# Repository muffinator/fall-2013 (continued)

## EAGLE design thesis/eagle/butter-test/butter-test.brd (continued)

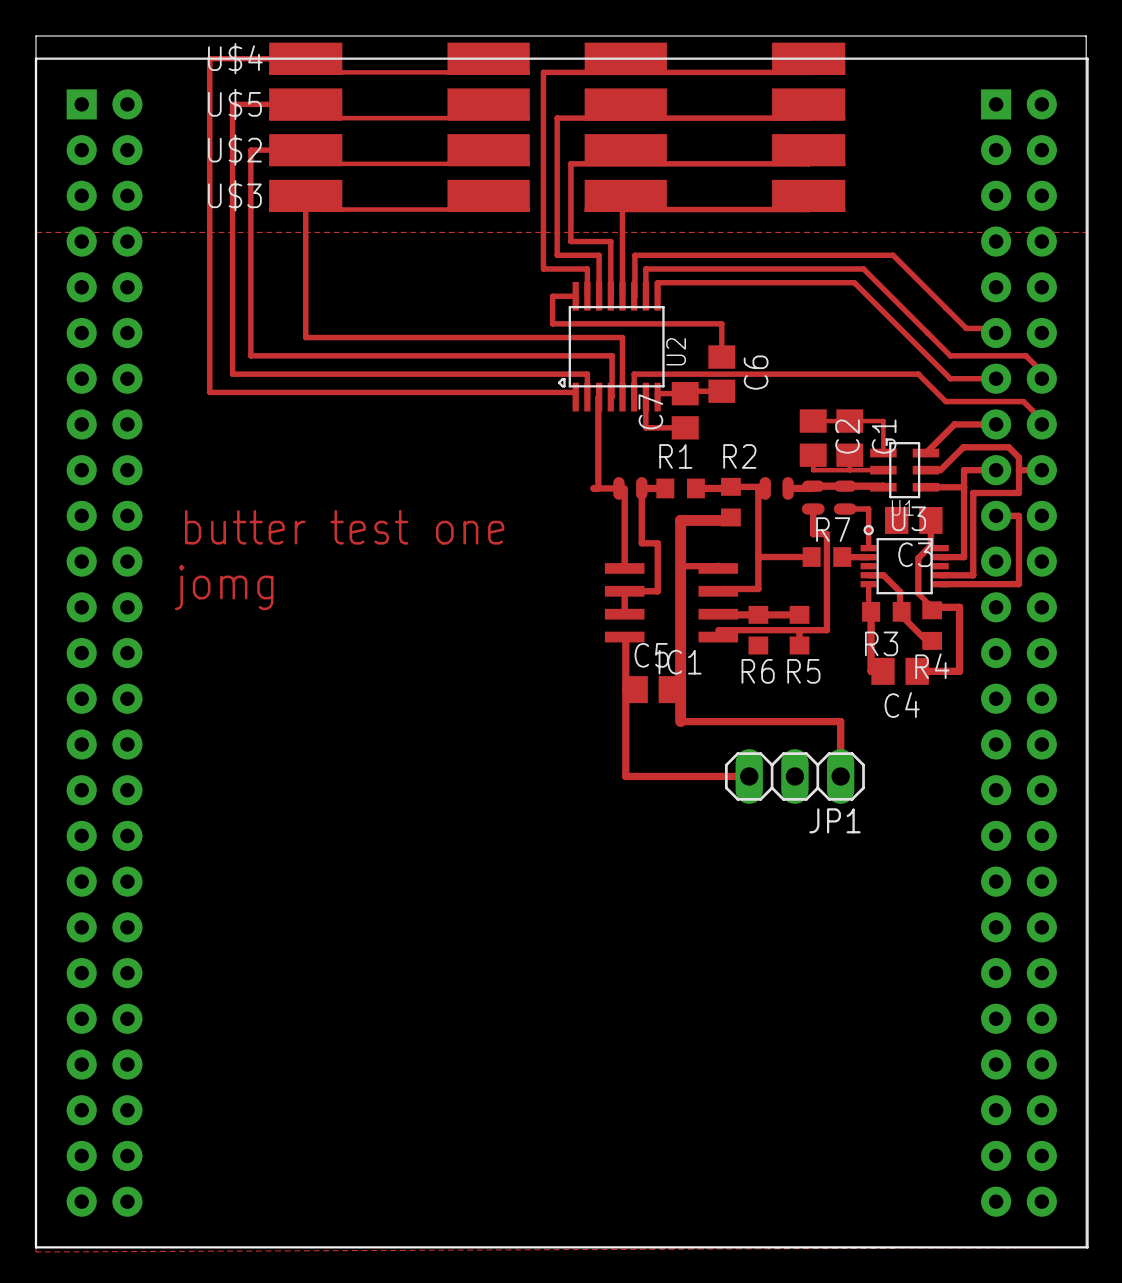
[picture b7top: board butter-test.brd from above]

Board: 2 copper layers, 58.3 x 67.3 mm, 28 parts (0 on the bottom side), 29 nets.

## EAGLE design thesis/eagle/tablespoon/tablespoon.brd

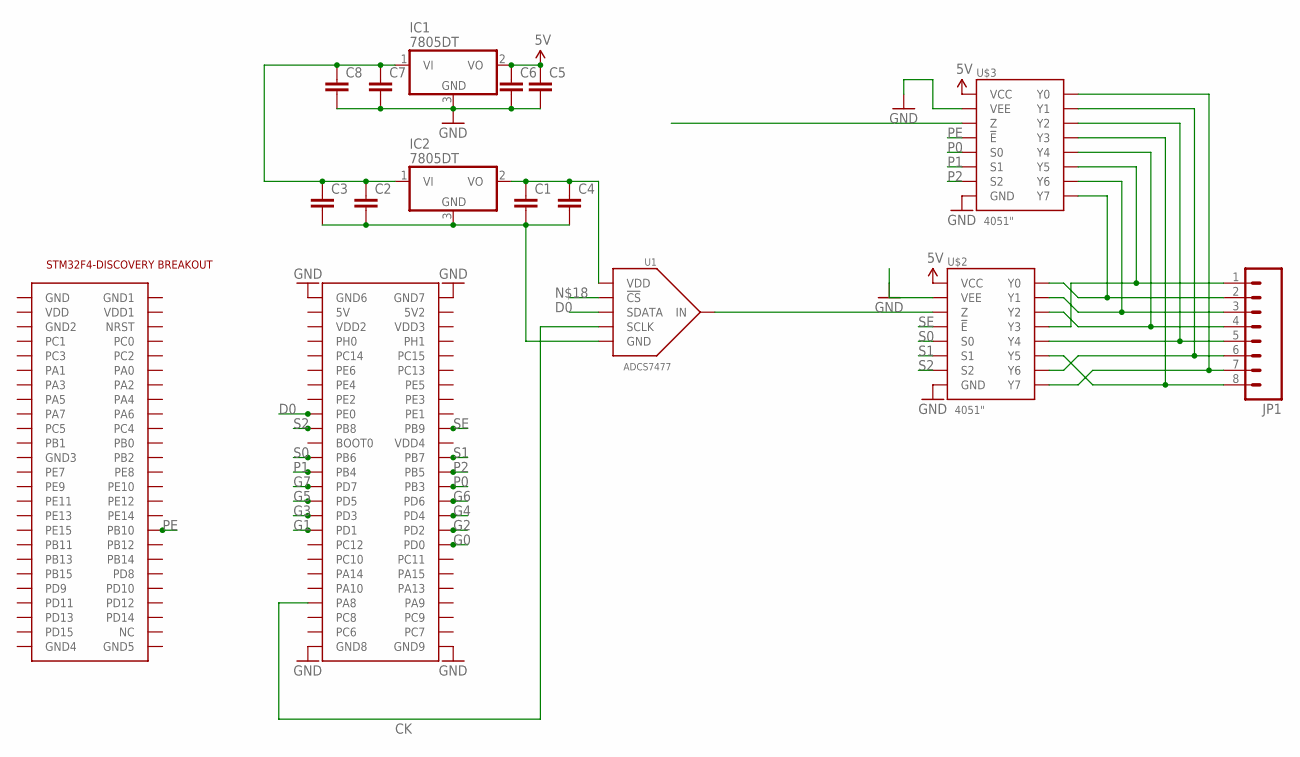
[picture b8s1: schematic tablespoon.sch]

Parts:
C1, C2, C3, C4, C5, C6, C7, C8: C-EUC0805; C0805
IC1, IC2: 7805DT; TO252
JP1: M08LONGPADS; 1X08_LONGPADS
U1: ADCS7477; SOT-23-6
U$1: STM32F4-DISCOVERY
U$2, U$3: 4051"; TSSOP-16

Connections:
5V: C5.1, C6.1, IC1.2 (VO), U$2.P$16 (VCC), U$3.P$16 (VCC)
CK: U1.P$4 (SCLK), U$1.P$93 (PA8)
D0: U1.P$5 (SDATA), U$1.P$67 (PE0)
G0: U$1.P$86 (PD0)
G1: U$1.P$83 (PD1)
G2: U$1.P$84 (PD2)
G3: U$1.P$81 (PD3)
G4: U$1.P$82 (PD4)
G5: U$1.P$79 (PD5)
G6: U$1.P$80 (PD6)
G7: U$1.P$77 (PD7)
GND: C5.2, C6.2, C7.2, C8.2, IC1.3 (GND), U$1.P$51 (GND6), U$1.P$52 (GND7), U$1.P$99 (GND8), U$1.P$100 (GND9), U$2.P$7 (VEE), U$2.P$8 (GND), U$3.P$7 (VEE), U$3.P$8 (GND)
unnamed: U1.P$3 (IN), U$2.P$3 (Z)
unnamed: C1.1, C4.1, IC2.2 (VO), U1.P$1 (VDD)
unnamed: C1.2, C2.2, C3.2, C4.2, IC2.3 (GND), U1.P$2 (GND)
unnamed: C2.1, C3.1, C7.1, C8.1, IC1.1 (VI), IC2.1 (VI)
unnamed: JP1.4, U$2.P$15 (Y2), U$3.P$1 (Y4)
unnamed: JP1.7, U$2.P$4 (Y7), U$3.P$13 (Y0)
unnamed: JP1.5, U$2.P$1 (Y4), U$3.P$15 (Y2)
unnamed: JP1.8, U$2.P$5 (Y5), U$3.P$12 (Y3)
unnamed: JP1.1, U$2.P$12 (Y3), U$3.P$5 (Y5)
unnamed: JP1.2, U$2.P$13 (Y0), U$3.P$4 (Y7)
unnamed: JP1.3, U$2.P$14 (Y1), U$3.P$2 (Y6)
unnamed: JP1.6, U$2.P$2 (Y6), U$3.P$14 (Y1)
P0: U$1.P$78 (PB3), U$3.P$11 (S0)
P1: U$1.P$75 (PB4), U$3.P$10 (S1)
P2: U$1.P$76 (PB5), U$3.P$9 (S2)
PE: U$1.P$34 (PB10), U$3.P$6 (!E)
S0: U$1.P$73 (PB6), U$2.P$11 (S0)
S1: U$1.P$74 (PB7), U$2.P$10 (S1)
S2: U$1.P$69 (PB8), U$2.P$9 (S2)
SE: U$1.P$70 (PB9), U$2.P$6 (!E)

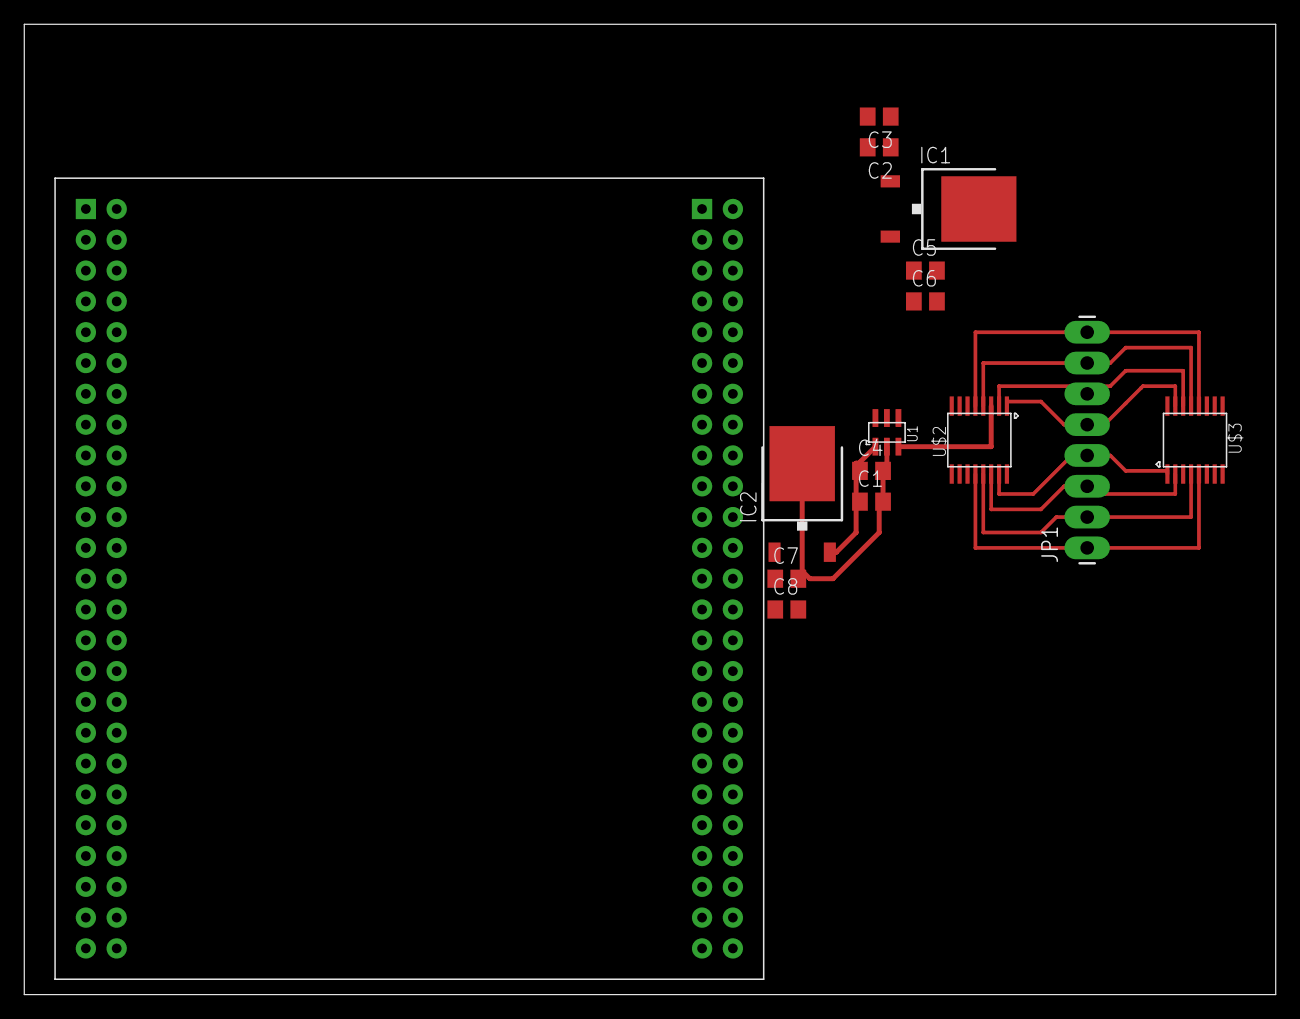
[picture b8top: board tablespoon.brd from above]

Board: 2 copper layers, 103.2 x 80.0 mm, 15 parts (0 on the bottom side), 24 nets.

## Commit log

2013-09-10 added readme
2013-09-10 added ps1 and ps2
2013-09-10 updated ps2
2013-09-10 added ps2, edited!
2013-09-11 finished writing up problems, just need to put in schematics
2013-09-11 added transistor datasheets
2013-09-11 corrected Vbe on problem 2
2013-09-11 finished ps2
2013-09-18 added ps3
2013-09-18 added gitignore
2013-09-18 finished problems 4 and 5
2013-09-19 finished text for pset 3
2013-09-19 finished pictures for pset 3
2013-09-19 added ce-max image
2013-09-19 almost finished ps3
2013-09-19 fixed pictures
2013-09-19 compiled final pset
2013-09-19 added extra credit section
2013-10-01 added ps4
2013-10-01 added pdf and tex
2013-10-01 finished pset 4
2013-10-01 added remaining ps4 images
2013-10-07 added bypassing caps on cascode current sources.
2013-10-07 pdflatex'd with new images
2013-10-16 added 6.332
2013-10-16 added solns for ps1
2013-10-17 added 6.301 ps5
2013-10-17 added ps5 images
2013-10-17 fixed cap label
2013-10-17 fixed node
2013-10-25 added 6.332 pset stuff
2013-10-25 added ps4 and 5 to 6.301
2013-10-25 added 6.332 project folder and ps2 info
2013-10-25 cleaning up
2013-11-05 added ps6 and 7
2013-11-12 added ps5 and 6 solns
2013-11-17 added ps4 solns and npn spice model example
2013-11-17 worked on resonant rectifier a bit
2013-11-17 added resonant-rect-orig
2013-11-17 worked on resonant rect: now 2.45 GHz
2013-11-18 took data modifying l_r and Vo and Iin
2013-11-18 added roberge's lab 2
2013-11-18 added no .raws to gitignore
2013-11-18 added 6.332 ps4
2013-11-18 cleanup + adding solutions
2013-11-18 nailed down Lr, Vo, and Iin
2013-11-18 data
2013-11-18 deleted .raws
2013-11-18 added rectifier layout
2013-11-18 added .fft to gitignore
2013-11-19 added ps8
2013-11-22 finished pset 8
2013-11-22 added recitation notes
2013-12-11 ps8 cleanup
2013-12-11 working on ps8 solns
2013-12-11 finished ps8 solns
2013-12-16 almost done with 332 project
2013-12-16 added ps9
2013-12-16 added final stuff for 6.301
2013-12-22 added psc
2013-12-22 added thesis
2014-10-31 iterates through all nodes specified for .op and prints out dictionaries for each simulation
2014-10-31 added sent proposal
2014-12-17 sim.py structure written
2014-12-17 removed output.txt
2014-12-17 added n-resistor attempt
2014-12-17 added d3 viewers and json examples
2014-12-17 added two-resistor network solver
2014-12-25 added some eagle files and .gitinit file
2014-12-25 added bom
2014-12-25 cleaning up ugly eagle files
2014-12-25 added eagle files for reals now
2014-12-25 added new flexible methods to sim.py, deleted sim.net, got n.py pretty much all the way working
2014-12-25 started playing with AC analysis
2014-12-25 stopped tracking json files
2014-12-25 ignoring datasheets, json files, and ugly eagle files
2014-12-26 ignoring .pyc's
2014-12-26 added stm32f4 part library
2014-12-26 added stm32f4 breakout to design, starting with two ADCs and two multiplexers
2014-12-27 started simulating breadboard rail drive solutions
2014-12-28 testing voltage and current based probing
2014-12-28 added analog switch to bom - will probably turn into nfet and pfet
2014-12-28 added rails to library
2014-12-28 started designing rail interface
2015-01-18 added breakout board
2015-01-18 added adc-in sim
2015-01-18 added breadboard 3d models
2015-01-18 voltage default played with
2015-01-18 added gluespot
2015-02-12 updated gitignore
2015-02-17 whatever, fuck it
2015-03-09 added muxes and pga to bom
2015-03-09 rev 1a!
2015-03-09 was playing with ADC input circuitry. I added the passive divider + offset circuit (R1 and R2) and decided to play with the other gain options
2015-03-09 first etch board rev. Doesn't have the switches on it (those have high capacitance, too :()
2015-03-10 added butter stm32 project
2015-03-14 butter folder commit
2015-03-14 renamed butter to butter-f3
2015-03-27 have timer two working and still trying to get the DMA working. realized a couple things - i'm using the CC interrupt on the timer, not the update one, and the DMA was configured for using the update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
2015-03-27 moved thesis parts to /thesis
2015-03-27 moved proposal stuff
2015-03-27 shrug
2015-03-30 output DMA to GPIOB working
2015-03-30 got 16MHz data->GPIOB working
2015-03-31 have triggered sampling working
2015-04-01 non-circular one-shot working, with end-of-transfer reset
2015-04-03 non-circular one-shot with timer 2 update interrupt disabling timer 1, then timer 1 re-enabled by other fuction
2015-04-06 have one-shot triggered by timer reset working
2015-04-06 send raw ADC buffer over USB
2015-04-07 maybe decoding works?
2015-04-08 have data-rearrangement working
2015-04-09 committing
2015-04-10 sending one datapoint to node.js working
2015-05-28 started rlc.py, fixed random metlist generation
2015-05-28 latest butter work
2015-05-28 got resistor force diagram working
2015-05-28 latest thesis writing
2015-06-02 got rlc to do steady state resistors with simple method
2015-06-02 modified note
2015-06-04 got AC simulation parsing working in sim.py, working on generating the impedance matrix for any given AC frequency data
2015-06-04 not sure what's new here, but updated butter board
2015-06-04 update gitignore
2015-06-25 streamlined voltage sampling
2015-06-25 worked on thesis a bit, started writing about resistor simulation
2015-06-25 added mosfet to library
2015-06-25 started working on a tablespoon of butter
2015-06-25 so I can read inductors and capacitors and resistors, but i haven't figured out how to select the correct frequency reading for each component yet. working on that now!
2015-06-25 r,l,and cboop are now only two dimensions
2015-06-25 have resistors working, need to get the diagonal of L and C
2015-06-25 made the frames smaller
2015-06-26 re-added zboop to do the diagonal
2015-06-26 can't seem to get the diagonal impedance method working...
2015-06-30 wrote so much more on my theeesiiiis
2015-06-30 rlc images for thesis
2015-07-09 added teaspoon!
2015-07-09 worked on thesis more?
2015-07-09 teaspoon as we know it (multiply by 2 issue)
2015-07-10 grounding, muxing, and ADCing all working. x2 fixed (had to do with number of packets sent over USB?????
2015-07-10 just a spoonful of sugar makes the medicine go down - python cereal controler for tsp
2015-07-10 took away those nasty usb subroutines and defines
2015-07-10 nona dose pesky blegh files, all right?!
2015-07-10 oh when you're done with that teaspoon, do i gotta tablespoon fer you!
2015-07-10 showing gjs this - pass 1
2015-07-11 if you slow down sampling, things get more accurate. re-wrote sample trigger 's' so it has a timing parameter and mux trigger 'm' so it has a gate parameter.
2015-07-19 peak detecting and thiiings
2015-07-19 moved all the eagle files into folders
2015-07-19 moved all the eagle stuff from /eagle to individual folders
2015-07-19 adding sine wavetable
2015-07-19 added .cir to gitignore
2015-07-19 switch-break
2015-07-19 made inductor and capacitor SVGs, played around with trying to graph RLC's
2015-07-27 added regression
2015-07-27 one timer interrupt at a time
2015-07-27 deleted extraneous files
2015-07-28 so, the timer counter was escaping the reset period, causing it to count to 4 billion until the next update event. fixed by forcing the timer back down to 0 on re-write.
2015-07-28 the diagonal in the generating matrix is no longer ground, it is simply an unconnected node. ground is added in during simulation, just like on the physical breadboard. this removes the need for the 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
2015-07-28 new .json writing with decimal places
2015-07-28 removing .cir and output files
2015-07-28 removing extraneous files
2015-07-28 fixed timing issue, got an RC recorded, working on high frequency recording and characterization
2015-07-30 DAC and ADC seem to be timed correctly. DAC is functional, something screwy with ADC
2015-07-30 fixed strange ADC issue by syncing DAC crossover... not exactly sure why this worked
2015-07-30 plotting impedance and voltage, added plot labels
2015-08-02 fft amplitude measure
2015-08-05 working on 8-channel DAC side
2015-08-05 blah blah
2015-08-05 playing with ajax??
2015-08-05 didn't do anything here
2015-08-05 working on component identification
2015-08-06 driving tablespoon
2015-08-06 moved the dimension over .01 inch
2015-08-06 whoops... put the components on the backside
2015-08-06 updated gitignore no png/pdf in eagle files
2015-08-06 try that
2015-08-06 try this
2015-08-06 new file, new gitignore
2015-08-07 added switch control, working out bugs
2015-08-07 added readme!
2015-08-07 get reloading working
2015-08-07 made current reading possible
2015-08-07 in limbo
2015-08-07 fixed lack of resistor divider on current amp
2015-08-09 removed timer 2, reconfigured DMA and timer 5 to handle it. now using the repeition counter on timer1!
2015-08-09 teaspoon's status before migrating to new timer code
2015-08-09 sugar's status before migriting to new timer code
2015-08-09 updated teaspoon with new timer code
2015-08-09 fully removed timer2
2015-08-12 did a little thesis work, reorganized - algorithm first, then software, then hardware
2015-08-12 going for the full-system on one board!
2015-08-12 uhh not sure what state these are in, but let's go for it
2015-08-12 tested for ADC clocking and DMAing - seems good!
2015-08-12 finished new board
2015-08-21 bit-shifted the data output to the left one bit... seemed like everything was doubled.
2015-08-21 back to where we were - taking capacitance readings and all
2015-08-21 regression up to date
2015-08-22 started working on oz
2015-08-23 Oz is working!
2015-08-23 repointed resistor.json to oz
2015-08-23 uptodate on thesis
2015-08-23 all up to date on constants and little things
2015-08-23 added new switch to lbr
2015-08-23 added new boards, but got the old one working!
2015-08-24 working
2015-08-27 did some thesis work
2015-08-27 lalalalala still working
2015-08-28 done with three-node network
2015-08-28 more thesis
2015-08-29 well, this is the new thesis doc
2015-08-30 workin' on chapter 4
2015-09-01 working workin
2015-09-01 added circuit png
2015-09-01 added images to tex files
2015-09-02 nearly done with hardware chapter
2015-09-02 added stls for breadboard jig
2015-09-03 workin on firmware
2015-09-03 added more images
2015-09-03 added comments to timer 1
2015-09-04 more work on ch5 and 6
2015-09-07 before trying to do finite difference
2015-09-07 fixed ac and sim
2015-09-07 moar thesis work
2015-09-07 finite difference images
2015-09-07 pretty much got chap 1,2,3,4 done
2015-09-08 added new images and i'm almost done i swear!
2015-09-08 working on results
2015-09-08 adding more images
2015-09-09 sooo close!
2015-09-09 well... temporary done!
2015-09-10 alskjdf
2015-09-11 draft 1
2015-09-11 turning it it
